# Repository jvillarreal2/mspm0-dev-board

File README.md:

# MSPM0G3507 Development Board

custom 2-layer development board designed in KiCad.

## Features
- USB-C input with ESD protection (USBLC6-2SC6)
- 3.3V LDO power regulation (SPX3819)
- MSPM0G3507 ARM Cortex-M0+ MCU at 80MHz
- 8MHz external crystal oscillator
- CH340E USB-UART converter for PC communication
- LIS2DH accelerometer over I2C
- SWD debug interface (Tag-Connect)
- Ground plane on B.Cu

## Tools
- KiCad 10.0
- JLCPCB for fabrication

## Status
REV A — Design complete, awaiting fabrication.
Not final — known improvements for REV B:
- Shorten HFXIN crystal trace (currently 14mm, target <5mm)
- Review CC1/CC2 pull-down resistor values for USB-PD compatibility

### 3D View

### PCB Layout

### Top Layer

### Bottom Layer

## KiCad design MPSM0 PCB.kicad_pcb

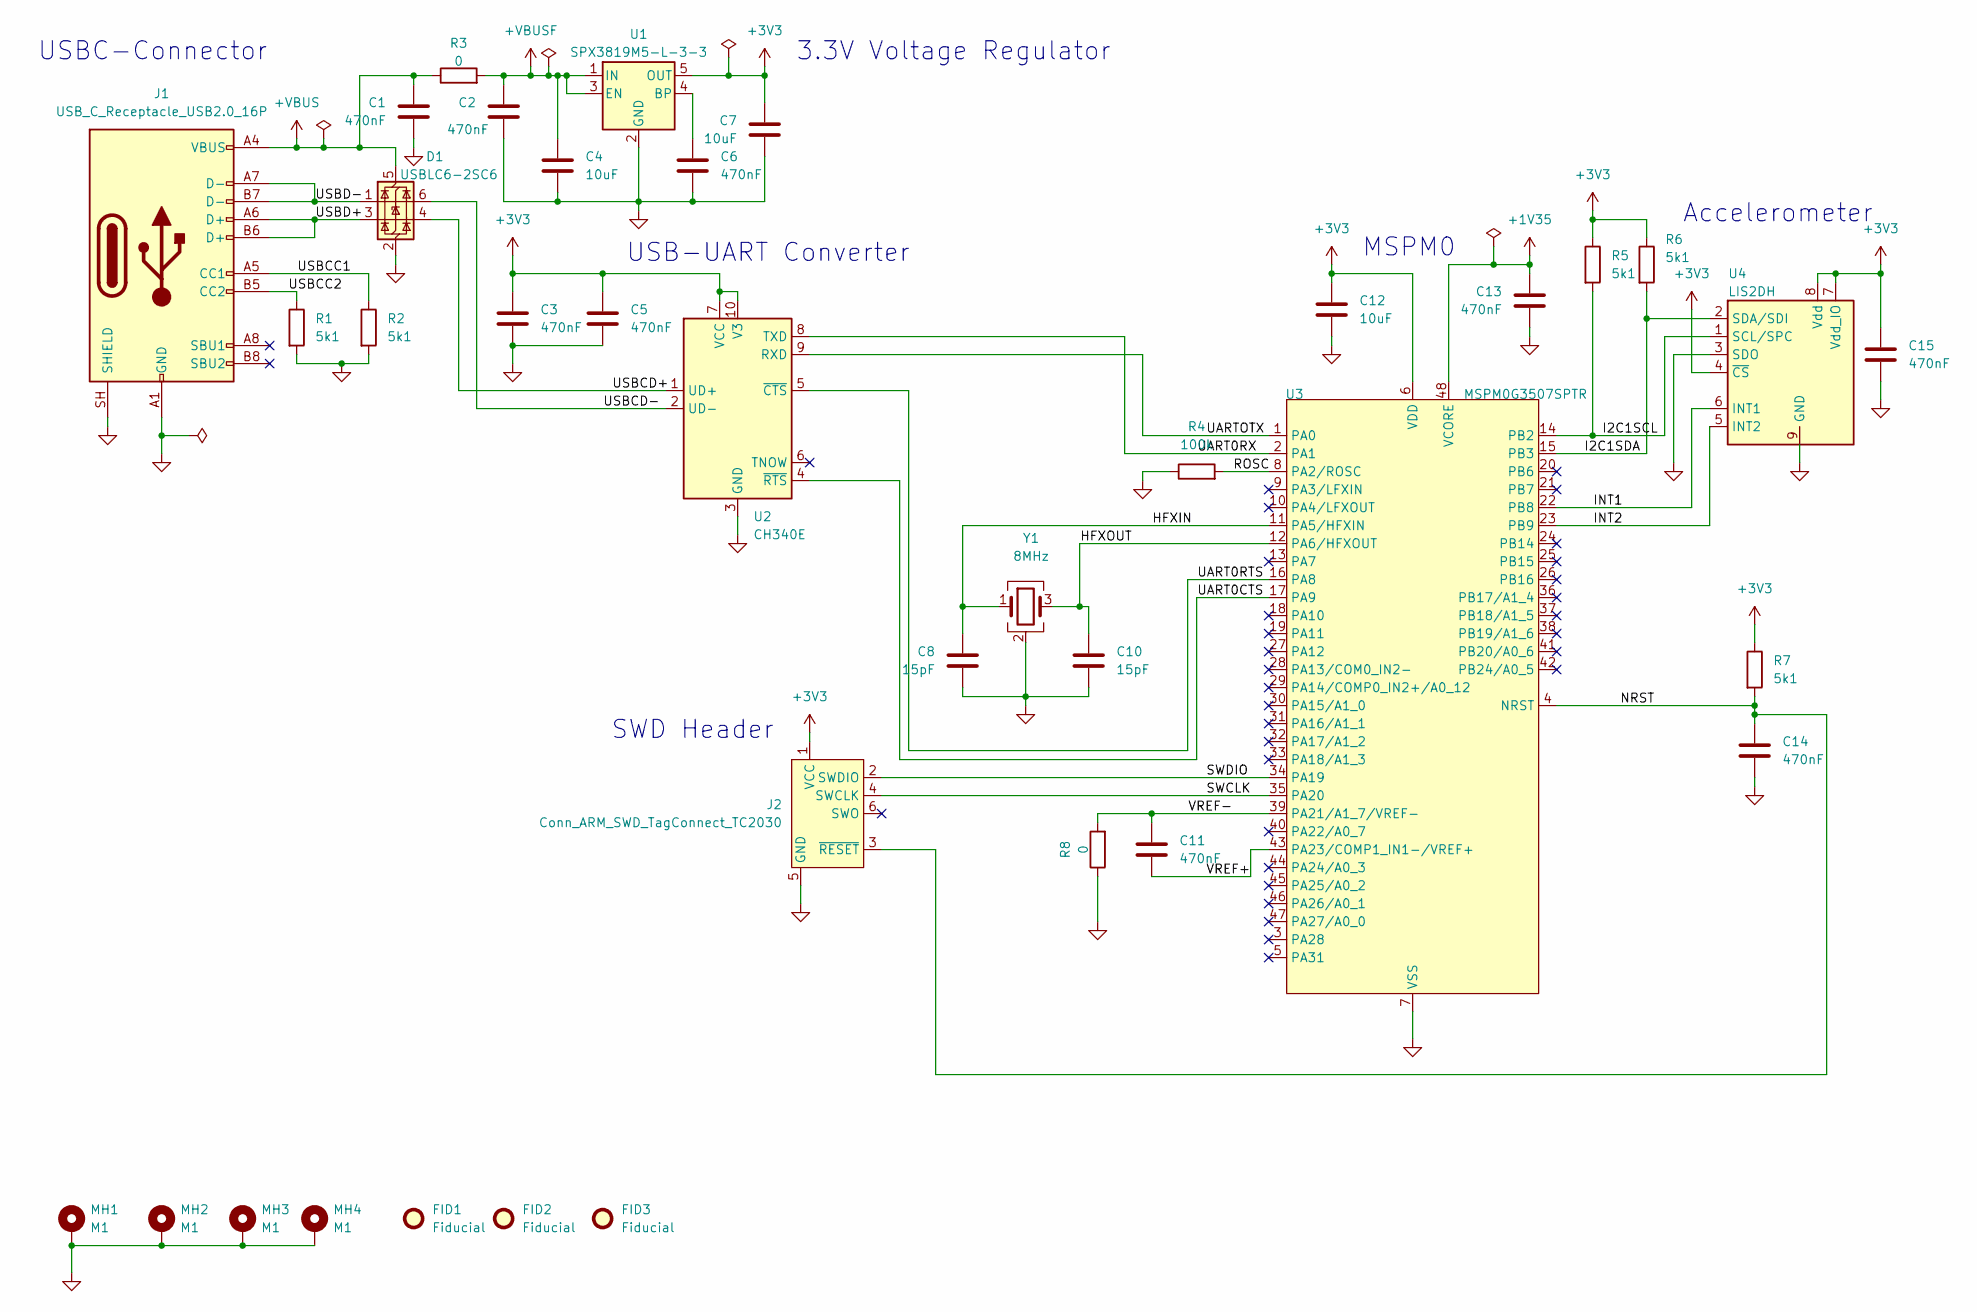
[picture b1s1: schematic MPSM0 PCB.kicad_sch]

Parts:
C1, C2, C3, C5, C6, C11, C13, C14, C15: 470nF; C_0603_1608Metric
C4, C7, C12: 10uF; C_0805_2012Metric
C8, C10: 15pF; C_0603_1608Metric
D1: USBLC6-2SC6; SOT-23-6
FID1, FID2, FID3: Fiducial; Fiducial_1mm_Mask2mm
J1: USB_C_Receptacle_USB2.0_16P; USB_C_Receptacle_GCT_USB4105-xx-A_16P_TopMnt_Horizontal
J2: Conn_ARM_SWD_TagConnect_TC2030; Tag-Connect_TC2030-IDC-FP_2x03_P1.27mm_Vertical
MH1, MH2, MH3, MH4: M1; MountingHole_3.2mm_M3_Pad_Via
R1, R2, R5, R6, R7: 5k1; R_0603_1608Metric
R3, R8: 0; R_0603_1608Metric
R4: 100k; R_0603_1608Metric
U1: SPX3819M5-L-3-3; SOT-23-5
U2: CH340E; MSOP-10_3x3mm_P0.5mm
U3: MSPM0G3507SPTR; LQFP-48_7x7mm_P0.5mm
U4: LIS2DH; LGA-14_2x2mm_P0.35mm_LayoutBorder3x4y
Y1: 8MHz; Crystal_SMD_3225-4Pin_3.2x2.5mm

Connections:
+1V35: C13.1, U3.48 (VCORE)
+3V3: C3.1, C5.1, C7.1, C12.1, C15.1, J2.1 (VCC), R5.1, R6.1, R7.1, U1.5 (OUT), U2.7 (VCC), U2.10 (V3), U3.6 (VDD), U4.4 (~CS), U4.7 (Vdd_IO), U4.8 (Vdd)
+VBUS: C1.1, D1.5 (VBUS), J1.A4 (VBUS), J1.A9 (VBUS), J1.B4 (VBUS), J1.B9 (VBUS), R3.1
+VBUSF: C2.1, C4.1, R3.2, U1.1 (IN), U1.3 (EN)
/HFXIN: C8.1, U3.11 (PA5/HFXIN), Y1.1
/HFXOUT: C10.1, U3.12 (PA6/HFXOUT), Y1.3
/I2C1SCL: R5.2, U3.14 (PB2), U4.1 (SCL/SPC)
/I2C1SDA: R6.2, U3.15 (PB3), U4.2 (SDA/SDI)
/INT1: U3.22 (PB8), U4.6 (INT1)
/INT2: U3.23 (PB9), U4.5 (INT2)
/NRST: C14.1, J2.3 (~RESET), R7.2, U3.4 (NRST)
/ROSC: R4.2, U3.8 (PA2/ROSC)
/SWCLK: J2.4 (SWCLK), U3.35 (PA20)
/SWDIO: J2.2 (SWDIO), U3.34 (PA19)
/UART0CTS: U2.4 (~RTS), U3.17 (PA9)
/UART0RTS: U2.5 (~CTS), U3.16 (PA8)
/UART0RX: U2.8 (TXD), U3.2 (PA1)
/UARTOTX: U2.9 (RXD), U3.1 (PA0)
/USBCC1: J1.A5 (CC1), R2.1
/USBCC2: J1.B5 (CC2), R1.1
/USBCD+: D1.4 (I/O2), U2.1 (UD+)
/USBCD-: D1.6 (I/O1), U2.2 (UD-)
/USBD+: D1.3 (I/O2), J1.A6 (D+), J1.B6 (D+)
/USBD-: D1.1 (I/O1), J1.A7 (D-), J1.B7 (D-)
/VREF+: C11.2, U3.43 (PA23/COMP1_IN1-/VREF+)
/VREF-: C11.1, R8.2, U3.39 (PA21/A1_7/VREF-)
GND: C1.2, C2.2, C3.2, C4.2, C5.2, C6.2, C7.2, C8.2, C10.2, C12.2, C13.2, C14.2, C15.2, D1.2 (GND), J1.A1 (GND), J1.A12 (GND), J1.B1 (GND), J1.B12 (GND), J1.SH (SHIELD), J2.5 (GND), MH1.1 (1_1), MH2.1 (1_1), MH3.1 (1_1), MH4.1 (1_1), R1.2, R2.2, R4.1, R8.1, U1.2 (GND), U2.3 (GND), U3.7 (VSS), U4.3 (SDO), U4.9 (GND), U4.10 (GND), U4.11 (GND), U4.12 (GND), U4.13 (GND), U4.14 (GND), Y1.2 (G), Y1.4 (G)
unnamed: C6.1, U1.4 (BP)

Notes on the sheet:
SWD Header
3.3V Voltage Regulator
USB-UART Converter
USBC-Connector
MSPM0
Accelerometer

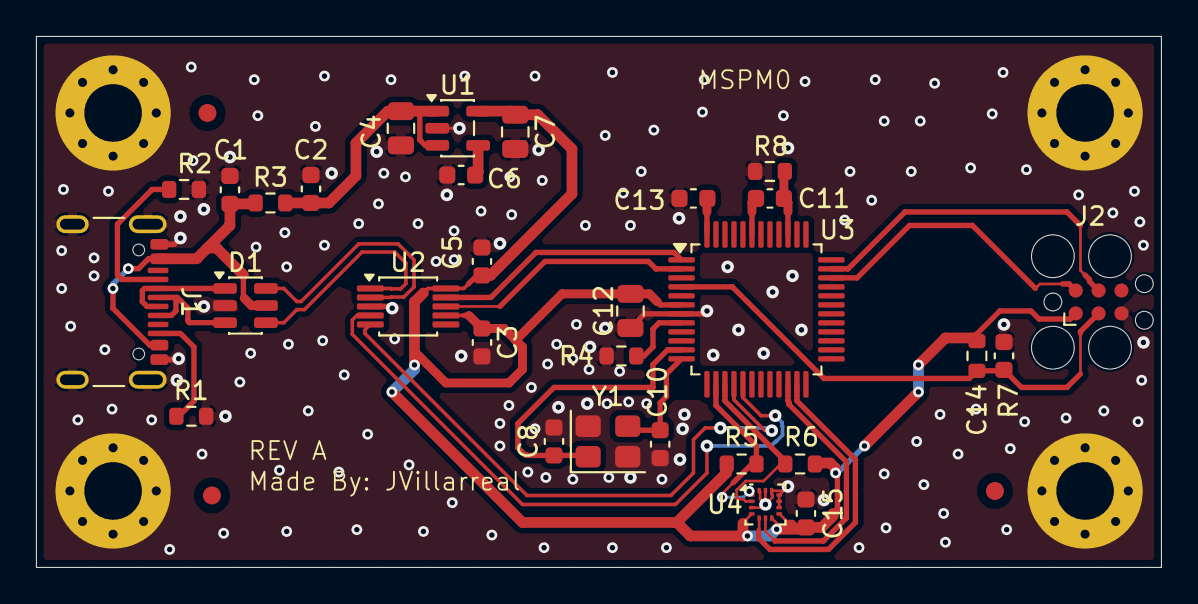
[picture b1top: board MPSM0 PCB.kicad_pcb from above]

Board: 2 copper layers, 62.5 x 29.5 mm, 37 parts (0 on the bottom side), 28 nets.

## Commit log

2026-03-28 Create txt
2026-03-28 Rename MPSM0 PCB.pdf to MPSM0_PCB.pdf
2026-03-28 Rename MPSM0_PCB.pdf to schematic.pdf
2026-03-28 Rename MPSM0 PCB.png to 3d_render.png
2026-03-28 Rename PCB layer_1.png to PCB_layer_1.png
2026-03-28 Rename PCB layer_2.png to PCB_layer_2.png
2026-03-28 Rename pcb layout.png to pcb_layout.png
